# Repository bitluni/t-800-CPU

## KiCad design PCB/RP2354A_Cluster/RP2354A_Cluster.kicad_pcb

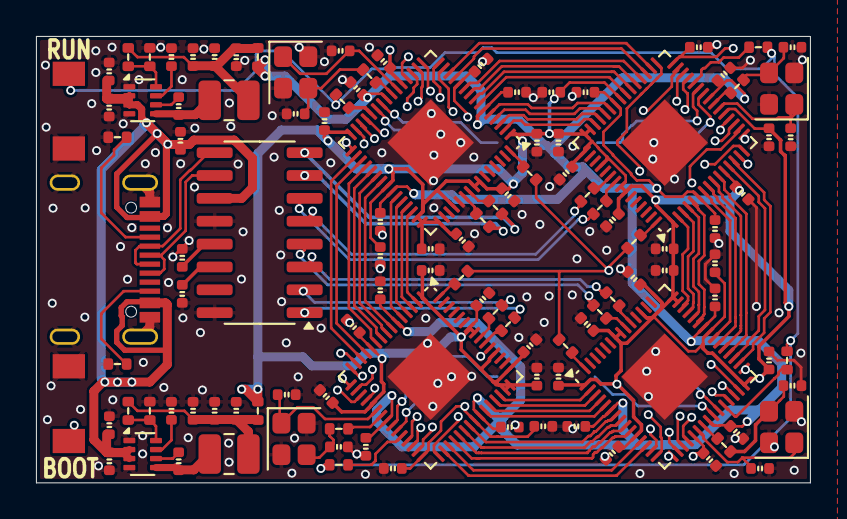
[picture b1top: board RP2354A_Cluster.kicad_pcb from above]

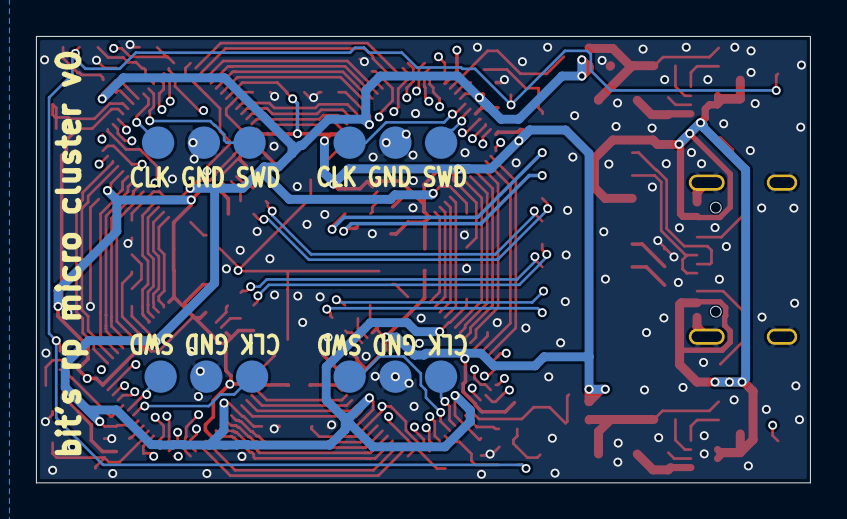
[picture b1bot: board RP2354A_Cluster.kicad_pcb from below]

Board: 4 copper layers, 43.0 x 24.8 mm, 117 parts (4 on the bottom side), 126 nets.

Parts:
C1, C2, C3, C4, C5, C6, C7, C8, C9, C10, C27, C28, C29, C30, C31, C32, C33, C34, C35, C36, C39, C40, C41, C42, C43, C44, C45, C46, C47, C48, C51, C52, C53, C54, C55, C56, C57, C58, C59, C60, C66, C72, C76, C77: 100n; C_0402_1005Metric
C11, C12, C25, C26, C37, C38, C49, C50: 15p; C_0402_1005Metric
C61, C62, C63, C64, C65, C67, C68, C70, C73, C74, C75: 10u; C_0402_1005Metric
C69, C71: 33n; C_0402_1005Metric
C78, C79, C80, C81: 4.7u; C_0402_1005Metric
L1: 1.8uH; L_1008_2520Metric
L2: 2.2uH; L_1008_2520Metric
R1, R2, R8, R9, R13, R14, R18, R19: 27; R_0402_1005Metric
R3, R22: 5.1k; R_0402_1005Metric
R4, R5, R6, R7, R10, R11, R12, R15, R16, R17, R20, R21: 1k; R_0402_1005Metric
R23, R28: 10k; R_0402_1005Metric
R24, R25: 0; R_0402_1005Metric
R26: 3.74k; R_0402_1005Metric
R27: 31.3k; R_0402_1005Metric
SW1, SW2: miniButton
TP1, TP2, TP3, TP4: TestPoint; Testpoint3
U13: SL2.1A; SOP-16_3.9x9.9mm_P1.27mm
U14: USB; USB-C
U15, U16: TPS62933; SOT-583-8
U17, U18, U19, U20: RP2340; QFN-60-1EP_7x7mm_P0.4mm_EP3.4x3.4mm
Y1, Y2, Y3, Y4: 12MHz GND24; Crystal_SMD_2520-4Pin_2.5x2.0mm

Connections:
+1.1V: C8.1, C9.1, C10.1, C27.1, C28.1, C29.1, C39.1, C40.1, C41.1, C51.1, C52.1, C53.1, R24.1, U17.6 (DVDD), U17.23 (DVDD), U17.39 (DVDD), U18.6 (DVDD), U18.23 (DVDD), U18.39 (DVDD), U19.6 (DVDD), U19.23 (DVDD), U19.39 (DVDD), U20.6 (DVDD), U20.23 (DVDD), U20.39 (DVDD)
+3.3V: C1.1, C2.1, C3.1, C4.1, C5.1, C6.1, C7.1, C30.1, C31.1, C32.1, C33.1, C34.1, C35.1, C36.1, C42.1, C43.1, C44.1, C45.1, C46.1, C47.1, C48.1, C54.1, C55.1, C56.1, C57.1, C58.1, C59.1, C60.1, C78.1, C79.1, C80.1, C81.1, R25.1, U17.1 (IOVDD), U17.11 (IOVDD), U17.20 (IOVDD), U17.30 (IOVDD), U17.38 (IOVDD), U17.44 (ADC_AVDD), U17.45 (IOVDD), U17.46 (VREG_AVDD), U17.49 (VREG_VIN), U17.53 (USB_OTP_VDD), U17.54 (QSPI_IOVDD), U18.1 (IOVDD), U18.11 (IOVDD), U18.20 (IOVDD), U18.30 (IOVDD), U18.38 (IOVDD), U18.44 (ADC_AVDD), U18.45 (IOVDD), U18.46 (VREG_AVDD), U18.49 (VREG_VIN), U18.53 (USB_OTP_VDD), U18.54 (QSPI_IOVDD), U19.1 (IOVDD), U19.11 (IOVDD), U19.20 (IOVDD), U19.30 (IOVDD), U19.38 (IOVDD), U19.44 (ADC_AVDD), U19.45 (IOVDD), U19.46 (VREG_AVDD), U19.49 (VREG_VIN), U19.53 (USB_OTP_VDD), U19.54 (QSPI_IOVDD), U20.1 (IOVDD), U20.11 (IOVDD), U20.20 (IOVDD), U20.30 (IOVDD), U20.38 (IOVDD), U20.44 (ADC_AVDD), U20.45 (IOVDD), U20.46 (VREG_AVDD), U20.49 (VREG_VIN), U20.53 (USB_OTP_VDD), U20.54 (QSPI_IOVDD)
+5V: C62.2, C64.2, C70.2, C76.2, C77.2, U13.11 (VCC5V), U14.2 (VBUS), U14.11 (VBUS), U15.2 (EN), U15.3 (VIN), U16.2 (EN), U16.3 (VIN)
/BUSAB_0: U17.43 (GPIO29_ADC3), U18.2 (GPIO0)
/BUSAB_1: U17.42 (GPIO28_ADC2), U18.3 (GPIO1)
/BUSAB_2: U17.41 (GPIO27_ADC1), U18.4 (GPIO2)
/BUSAB_3: U17.40 (GPIO26_ADC0), U18.5 (GPIO3)
/BUSAB_4: U17.37 (GPIO25), U18.7 (GPIO4)
/BUSAB_5: U17.36 (GPIO24), U18.8 (GPIO5)
/BUSAB_6: U17.35 (GPIO23), U18.9 (GPIO6)
/BUSAB_7: U17.34 (GPIO22), U18.10 (GPIO7)
/BUSAB_8: U17.33 (GPIO21), U18.12 (GPIO8)
/BUSAB_9: U17.32 (GPIO20), U18.13 (GPIO9)
/BUSAC_0: U17.14 (GPIO10), U19.14 (GPIO10)
/BUSAC_1: U17.15 (GPIO11), U19.15 (GPIO11)
/BUSAC_2: U17.16 (GPIO12), U19.16 (GPIO12)
/BUSAC_3: U17.17 (GPIO13), U19.17 (GPIO13)
/BUSAC_4: U17.18 (GPIO14), U19.18 (GPIO14)
/BUSAC_5: U17.19 (GPIO15), U19.19 (GPIO15)
/BUSAC_6: U17.27 (GPIO16), U19.27 (GPIO16)
/BUSAC_7: U17.28 (GPIO17), U19.28 (GPIO17)
/BUSAC_8: U17.29 (GPIO18), U19.29 (GPIO18)
/BUSAC_9: U17.31 (GPIO19), U19.31 (GPIO19)
/BUSAD_0: U17.2 (GPIO0), U20.43 (GPIO29_ADC3)
/BUSAD_1: U17.3 (GPIO1), U20.42 (GPIO28_ADC2)
/BUSAD_2: U17.4 (GPIO2), U20.41 (GPIO27_ADC1)
/BUSAD_3: U17.5 (GPIO3), U20.40 (GPIO26_ADC0)
/BUSAD_4: U17.7 (GPIO4), U20.37 (GPIO25)
/BUSAD_5: U17.8 (GPIO5), U20.36 (GPIO24)
/BUSAD_6: U17.9 (GPIO6), U20.35 (GPIO23)
/BUSAD_7: U17.10 (GPIO7), U20.34 (GPIO22)
/BUSAD_8: U17.12 (GPIO8), U20.33 (GPIO21)
/BUSAD_9: U17.13 (GPIO9), U20.32 (GPIO20)
/BUSBC_0: U18.43 (GPIO29_ADC3), U19.2 (GPIO0)
/BUSBC_1: U18.42 (GPIO28_ADC2), U19.3 (GPIO1)
/BUSBC_2: U18.41 (GPIO27_ADC1), U19.4 (GPIO2)
/BUSBC_3: U18.40 (GPIO26_ADC0), U19.5 (GPIO3)
/BUSBC_4: U18.37 (GPIO25), U19.7 (GPIO4)
/BUSBC_5: U18.36 (GPIO24), U19.8 (GPIO5)
/BUSBC_6: U18.35 (GPIO23), U19.9 (GPIO6)
/BUSBC_7: U18.34 (GPIO22), U19.10 (GPIO7)
/BUSBC_8: U18.33 (GPIO21), U19.12 (GPIO8)
/BUSBC_9: U18.32 (GPIO20), U19.13 (GPIO9)
/BUSBD_0: U18.14 (GPIO10), U20.14 (GPIO10)
/BUSBD_1: U18.15 (GPIO11), U20.15 (GPIO11)
/BUSBD_2: U18.16 (GPIO12), U20.16 (GPIO12)
/BUSBD_3: U18.17 (GPIO13), U20.17 (GPIO13)
/BUSBD_4: U18.18 (GPIO14), U20.18 (GPIO14)
/BUSBD_5: U18.19 (GPIO15), U20.19 (GPIO15)
/BUSBD_6: U18.27 (GPIO16), U20.27 (GPIO16)
/BUSBD_7: U18.28 (GPIO17), U20.28 (GPIO17)
/BUSBD_8: U18.29 (GPIO18), U20.29 (GPIO18)
/BUSBD_9: U18.31 (GPIO19), U20.31 (GPIO19)
/BUSCD_0: U19.43 (GPIO29_ADC3), U20.2 (GPIO0)
/BUSCD_1: U19.42 (GPIO28_ADC2), U20.3 (GPIO1)
/BUSCD_2: U19.41 (GPIO27_ADC1), U20.4 (GPIO2)
/BUSCD_3: U19.40 (GPIO26_ADC0), U20.5 (GPIO3)
/BUSCD_4: U19.37 (GPIO25), U20.7 (GPIO4)
/BUSCD_5: U19.36 (GPIO24), U20.8 (GPIO5)
/BUSCD_6: U19.35 (GPIO23), U20.9 (GPIO6)
/BUSCD_7: U19.34 (GPIO22), U20.10 (GPIO7)
/BUSCD_8: U19.33 (GPIO21), U20.12 (GPIO8)
/BUSCD_9: U19.32 (GPIO20), U20.13 (GPIO9)
/DA+: R1.2, U13.8 (DP1)
/DA-: R2.2, U13.7 (DM1)
/DB+: R8.2, U13.2 (DP4)
/DB-: R9.2, U13.1 (DM4)
/DC+: R18.2, U13.6 (DP2)
/DC-: R19.2, U13.5 (DM2)
/DD+: R13.2, U13.4 (DP3)
/DD-: R14.2, U13.3 (DM3)
/RUN: R5.2, R10.2, R15.2, R20.2, SW1.2
/UDM: U13.9 (UDM), U14.5 (DN2), U14.7 (DN1)
/UDP: U13.10 (UDP), U14.6 (DP1), U14.8 (DP2)
/~USB_BOOT: R6.2, R7.2, R12.2, R17.2, SW2.2
GND: C1.2, C2.2, C3.2, C4.2, C5.2, C6.2, C7.2, C8.2, C9.2, C10.2, C11.1, C12.1, C25.1, C26.1, C27.2, C28.2, C29.2, C30.2, C31.2, C32.2, C33.2, C34.2, C35.2, C36.2, C37.1, C38.1, C39.2, C40.2, C41.2, C42.2, C43.2, C44.2, C45.2, C46.2, C47.2, C48.2, C49.1, C50.1, C51.2, C52.2, C53.2, C54.2, C55.2, C56.2, C57.2, C58.2, C59.2, C60.2, C61.1, C62.1, C63.1, C64.1, C65.1, C67.1, C68.1, C69.1, C70.1, C71.1, C73.1, C74.1, C75.1, C76.1, C77.1, C78.2, C79.2, C80.2, C81.2, R3.1, R22.2, R23.1, R28.1, SW1.1, SW2.1, TP1.2, TP2.2, TP3.2, TP4.2, U13.12 (GND), U13.16 (XIN), U14.0 (Shield), U14.1 (GND), U14.12 (GND), U15.1 (RT), U15.4 (GND), U16.1 (RT), U16.4 (GND), U17.47 (VREG_PGND), U17.50 (VREG_FB), U17.61 (GND), U18.47 (VREG_PGND), U18.50 (VREG_FB), U18.61 (GND), U19.47 (VREG_PGND), U19.50 (VREG_FB), U19.61 (GND), U20.47 (VREG_PGND), U20.50 (VREG_FB), U20.61 (GND), Y1.2, Y1.4, Y2.2, Y2.4, Y3.2, Y3.4, Y4.2, Y4.4
unnamed: C12.2, R4.2, Y1.3
unnamed: C26.2, R11.2, Y2.3
unnamed: C38.2, R16.2, Y3.3
unnamed: C50.2, R21.2, Y4.3
unnamed: C65.2, C67.2, C68.2, L1.1, R24.2, R26.2
unnamed: C73.2, C74.2, C75.2, L2.1, R25.2, R27.2
unnamed: C63.2, U13.13 (VDD3)
unnamed: C61.2, U13.14 (VDD18)
unnamed: R3.2, U14.4 (CC1)
unnamed: R22.1, U14.10 (CC2)
unnamed: C66.2, U15.6 (BST)
unnamed: R23.2, R26.1, U15.8 (FB)
unnamed: C69.2, U15.7 (SS)
unnamed: C66.1, L1.2, U15.5 (SW)
unnamed: C72.2, U16.6 (BST)
unnamed: R27.1, R28.2, U16.8 (FB)
unnamed: C71.2, U16.7 (SS)
unnamed: C72.1, L2.2, U16.5 (SW)
unnamed: R6.1, U17.60 (QSPI_SS)
unnamed: R5.1, U17.26 (RUN)
unnamed: TP1.3, U17.24 (SWCLK)
unnamed: TP1.1, U17.25 (SWDIO)
unnamed: R2.1, U17.51 (USB_DM)
unnamed: R1.1, U17.52 (USB_DP)
unnamed: C11.2, U17.21 (XIN), Y1.1
unnamed: R4.1, U17.22 (XOUT)
unnamed: R7.1, U18.60 (QSPI_SS)
unnamed: R10.1, U18.26 (RUN)
unnamed: TP2.3, U18.24 (SWCLK)
unnamed: TP2.1, U18.25 (SWDIO)
unnamed: R9.1, U18.51 (USB_DM)
unnamed: R8.1, U18.52 (USB_DP)
unnamed: C25.2, U18.21 (XIN), Y2.1
unnamed: R11.1, U18.22 (XOUT)
unnamed: R12.1, U19.60 (QSPI_SS)
unnamed: R15.1, U19.26 (RUN)
unnamed: TP3.3, U19.24 (SWCLK)
unnamed: TP3.1, U19.25 (SWDIO)
unnamed: R14.1, U19.51 (USB_DM)
unnamed: R13.1, U19.52 (USB_DP)
unnamed: C37.2, U19.21 (XIN), Y3.1
unnamed: R16.1, U19.22 (XOUT)
unnamed: R17.1, U20.60 (QSPI_SS)
unnamed: R20.1, U20.26 (RUN)
unnamed: TP4.3, U20.24 (SWCLK)
unnamed: TP4.1, U20.25 (SWDIO)
unnamed: R19.1, U20.51 (USB_DM)
unnamed: R18.1, U20.52 (USB_DP)
unnamed: C49.2, U20.21 (XIN), Y4.1
unnamed: R21.1, U20.22 (XOUT)

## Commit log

2026-01-07 Add initial content to README.md
2026-01-07 Update README to clarify board status
2026-01-08 fixed power stuff
2026-01-08 removed extra traces
